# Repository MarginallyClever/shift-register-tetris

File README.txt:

Arduino Tetris clone : Learning basics of Arduino programming and circuit design with LEDs and DIY games.

2016-12-17 Dan Royer (dan@marginallyclever.com) 

See https://www.marginallyclever.com/2017/02/shared-anodes-and-cathodes/
for the tutorial, discussion, and lots of other great stuff.

Please support our work: Like, share, and buy from marginallyclever.com today.  Thank you!

Tetris brand copyright The Tetris Company.
All code CC-BY-NC-SA 2016 Marginally Clever Robots, Limited.

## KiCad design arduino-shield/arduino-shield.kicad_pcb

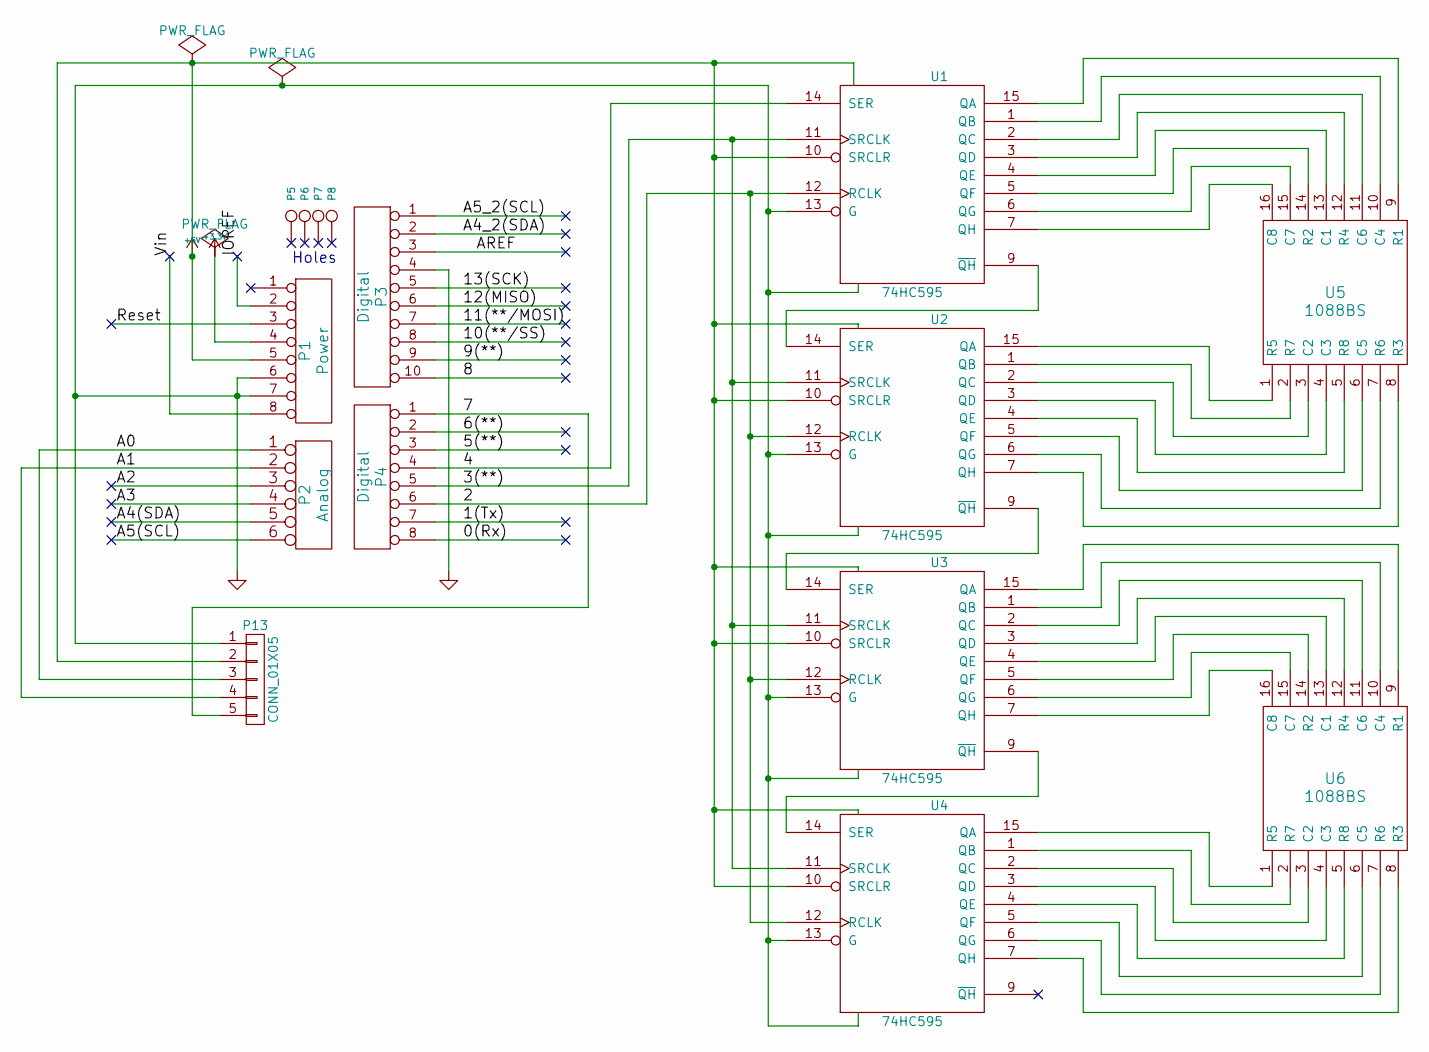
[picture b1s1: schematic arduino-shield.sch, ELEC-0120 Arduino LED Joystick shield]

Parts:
P1: Power; Socket_Strip_Arduino_1x08
P2: Analog; Socket_Strip_Arduino_1x06
P3: Digital; Socket_Strip_Arduino_1x10
P4: Digital; Socket_Strip_Arduino_1x08
P5, P6, P7, P8: CONN_1; Arduino_1pin
P13: CONN_01X05; Socket_Strip_Straight_1x05_Pitch2.54mm
U1, U2, U3, U4: 74HC595; DIP-16_W7.62mm
U5, U6: 1088BS

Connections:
+3V3: P1.4
+5V: P1.5, P13.2, U1.10 (SRCLR), U1.16 (VCC), U2.10 (SRCLR), U2.16 (VCC), U3.10 (SRCLR), U3.16 (VCC), U4.10 (SRCLR), U4.16 (VCC)
/0(Rx): P4.8
/1(Tx): P4.7
/2: P4.6, U1.12 (RCLK), U2.12 (RCLK), U3.12 (RCLK), U4.12 (RCLK)
/3(**): P4.5, U1.11 (SRCLK), U2.11 (SRCLK), U3.11 (SRCLK), U4.11 (SRCLK)
/4: P4.4, U1.14 (SER)
/5(**): P4.3
/6(**): P4.2
/7: P4.1, P13.5
/8: P3.10
/9(**): P3.9
/10(**/SS): P3.8
/11(**/MOSI): P3.7
/12(MISO): P3.6
/13(SCK): P3.5
/A0: P2.1, P13.3
/A1: P2.2, P13.4
/A2: P2.3
/A3: P2.4
/A4(SDA): P2.5
/A4_2(SDA): P3.2
/A5(SCL): P2.6
/A5_2(SCL): P3.1
/AREF: P3.3
/IOREF: P1.2
/Reset: P1.3
/Vin: P1.8
GND: P1.6, P1.7, P3.4, P13.1, U1.8 (GND), U1.13 (G), U2.8 (GND), U2.13 (G), U3.8 (GND), U3.13 (G), U4.8 (GND), U4.13 (G)
unnamed: U1.1 (QB), U5.10 (C4)
unnamed: U1.2 (QC), U5.11 (C6)
unnamed: U1.3 (QD), U5.12 (R4)
unnamed: U1.4 (QE), U5.13 (C1)
unnamed: U1.5 (QF), U5.14 (R2)
unnamed: U1.6 (QG), U5.15 (C7)
unnamed: U1.7 (QH), U5.16 (C8)
unnamed: U1.9 (~QH), U2.14 (SER)
unnamed: U1.15 (QA), U5.9 (R1)
unnamed: U2.1 (QB), U5.2 (R7)
unnamed: U2.2 (QC), U5.3 (C2)
unnamed: U2.3 (QD), U5.4 (C3)
unnamed: U2.4 (QE), U5.5 (R8)
unnamed: U2.5 (QF), U5.6 (C5~)
unnamed: U2.6 (QG), U5.7 (R6)
unnamed: U2.7 (QH), U5.8 (R3)
unnamed: U2.9 (~QH), U3.14 (SER)
unnamed: U2.15 (QA), U5.1 (R5)
unnamed: U3.1 (QB), U6.10 (C4)
unnamed: U3.2 (QC), U6.11 (C6)
unnamed: U3.3 (QD), U6.12 (R4)
unnamed: U3.4 (QE), U6.13 (C1)
unnamed: U3.5 (QF), U6.14 (R2)
unnamed: U3.6 (QG), U6.15 (C7)
unnamed: U3.7 (QH), U6.16 (C8)
unnamed: U3.9 (~QH), U4.14 (SER)
unnamed: U3.15 (QA), U6.9 (R1)
unnamed: U4.1 (QB), U6.2 (R7)
unnamed: U4.2 (QC), U6.3 (C2)
unnamed: U4.3 (QD), U6.4 (C3)
unnamed: U4.4 (QE), U6.5 (R8)
unnamed: U4.5 (QF), U6.6 (C5~)
unnamed: U4.6 (QG), U6.7 (R6)
unnamed: U4.7 (QH), U6.8 (R3)
unnamed: U4.15 (QA), U6.1 (R5)

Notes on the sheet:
Holes

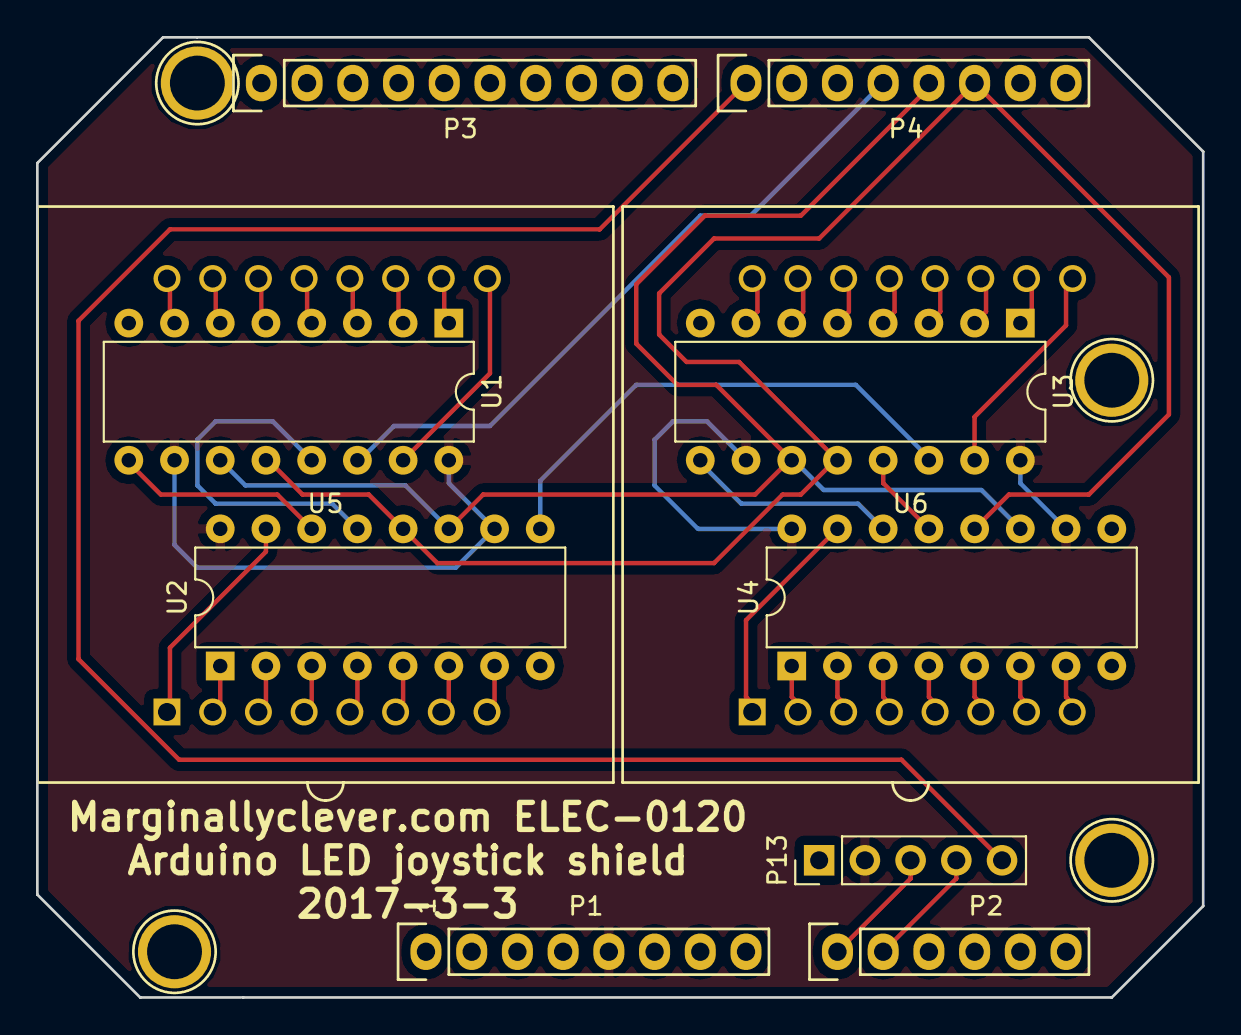
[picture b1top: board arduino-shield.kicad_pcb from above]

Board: 2 copper layers, 64.8 x 53.3 mm, 15 parts (0 on the bottom side), 43 nets.

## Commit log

2017-03-09 :lollipop: Added .gitattributes & .gitignore files
2017-03-09 added sorting pins openoffice sheets
